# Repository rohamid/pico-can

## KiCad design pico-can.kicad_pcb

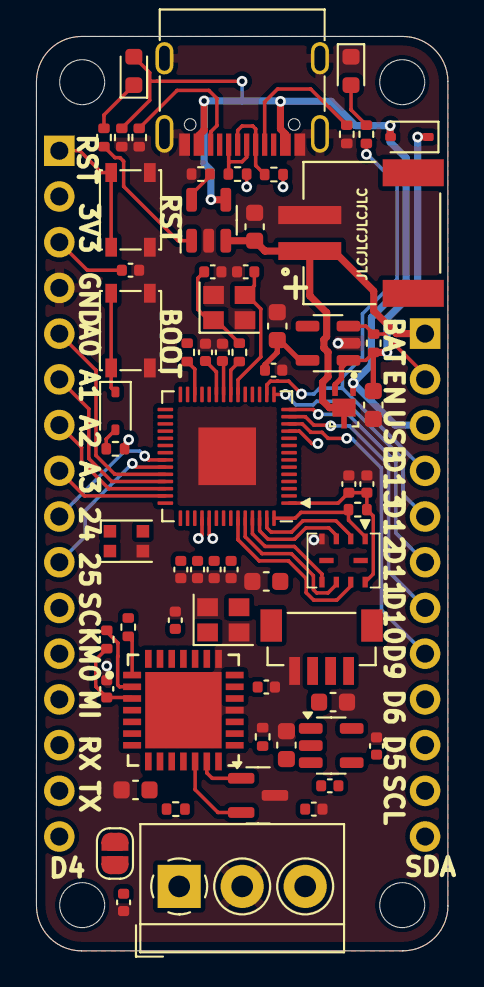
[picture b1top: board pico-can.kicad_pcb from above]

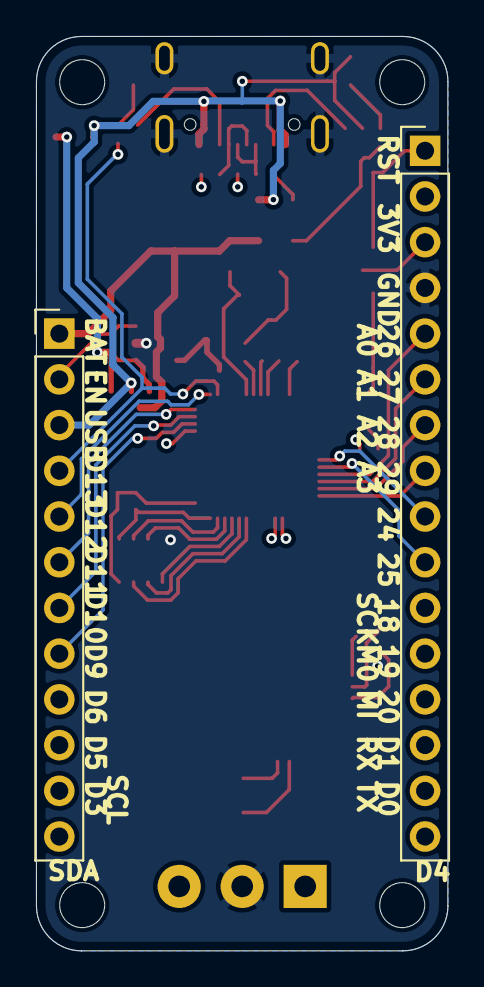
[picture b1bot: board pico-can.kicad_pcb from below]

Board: 2 copper layers, 22.9 x 50.8 mm, 71 parts (2 on the bottom side), 62 nets.

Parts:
C1, C2, C6, C18: 22p; C_0402_1005Metric
C3, C4, C5: 10u; C_0603_1608Metric
C7, C8, C10, C11, C12, C13, C14, C15, C16, C22, C23, C24: 100nF; C_0402_1005Metric
C9: 1uF; C_0402_1005Metric
C17, C21, C25, C26: 1uF; C_0603_1608Metric
C19, C20: 47pF; C_0402_1005Metric
D1: MBR0540; D_SOD-323
D2, D4: LED; LED_0603_1608Metric
D3: NSR0320; D_SOD-323
D5: WS2812B; LED_WS2812B-2020_PLCC4_2.0x2.0mm
D6: PESD1CAN; SOT-23
H1, H2, H3, H4: MountingHole; MountingHole_2.5mm
J1: USB_C_Receptacle_USB2.0; USB_C_Receptacle_G-Switch_GT-USB-7010ASV
J2: I2C; JST_BM04B-SRSS-TB_LF__SN_
J3: Screw_Terminal_01x03; TerminalBlock_4Ucon_1x03_P3.50mm_Horizontal
J4: Conn; PinHeader_1x16_P2.54mm_Vertical
J5: Conn; PinHeader_1x12_P2.54mm_Vertical
J6: BAT; JST_S2B-PH-SM4-TB_LF__SN_
JP1: JMP; SolderJumper-2_P1.3mm_Open_RoundedPad1.0x1.5mm
Q1: BSS83P; TRANS_DMG3415UFY4Q-7
R1, R3, R8, R9, R11, R12, R13, R14, R15, R16: 10K; R_0402_1005Metric
R2: 1K; R_0402_1005Metric
R4, R5, R10: 5K1; R_0402_1005Metric
R6, R7: 220; R_0402_1005Metric
R17: 120; R_0402_1005Metric
SW1, SW2: SW_Push; SW_SPST_PTS810
U1: RP2040; QFN-56-1EP_7x7mm_P0.4mm_EP3.2x3.2mm
U2: W25Q128JVS; USON-8-3x4
U3: AP2112K-3.3; SOT-23-5
U4: MCP73831; SOT-23-5
U5: AP3012; SOT-23-5
U7: MCP25625T-E_ML; Microchip-ML-28-0-0-0
Y1: 24MHz; Crystal_SMD_2520-4Pin_2.5x2.0mm
Y2: 16MHz; Crystal_SMD_2520-4Pin_2.5x2.0mm

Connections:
+1V2: C7.1, C8.1, C9.1, U1.23 (DVDD), U1.45 (VREG_VOUT), U1.50 (DVDD)
+3V3: C4.1, C10.1, C11.1, C12.1, C13.1, C14.1, C15.1, C16.1, C17.1, C21.1, C22.1, C23.1, C25.1, C26.1, J2.2, J4.2, J4.3, R1.1, R3.1, R14.1, R15.1, U1.1 (IOVDD), U1.10 (IOVDD), U1.22 (IOVDD), U1.33 (IOVDD), U1.42 (IOVDD), U1.43 (ADC_AVDD), U1.44 (VREG_IN), U1.48 (USB_VDD), U1.49 (IOVDD), U2.8 (VCC), U3.5 (VOUT), U7.3 (VDD), U7.11 (VIO)
/CAN-Bus/CANH: C19.1, D6.1 (K), J3.3, JP1.2 (B), U7.13 (CANH)
/CAN-Bus/CANL: C20.1, D6.2 (K), J3.1, R17.2, U7.12 (CANL)
/CAN-Bus/CAN_STBY: R16.2, U7.15 (STBY)
/CAN-Bus/RxCAN: U7.5 (RxCAN), U7.10 (RXD)
/CAN-Bus/TxCAN: U7.4 (TxCAN), U7.16 (TXD)
/CAN-Bus/~CAN_CS: R14.2, U7.1 (~CS)
/CAN-Bus/~CAN_RESET: R15.2, U7.2 (~RESET)
/EN: J5.2, R9.2, U3.3 (EN)
/GPIO0: J4.15, U1.2 (GPIO0)
/GPIO1: J4.14, U1.3 (GPIO1)
/GPIO2: J2.3, J5.12, U1.4 (GPIO2)
/GPIO3: J2.4, J5.11, U1.5 (GPIO3)
/GPIO4: J4.16, U1.6 (GPIO4)
/GPIO5: J5.10, U1.7 (GPIO5)
/GPIO6: J5.9, U1.8 (GPIO6)
/GPIO8: J4.13, U1.11 (GPIO8)
/GPIO9: J5.8, U1.12 (GPIO9)
/GPIO10: J5.7, U1.13 (GPIO10)
/GPIO11: J5.6, U1.14 (GPIO11)
/GPIO12: J5.5, U1.15 (GPIO12)
/GPIO13: J5.4, R13.1, U1.16 (GPIO13)
/GPIO14: J4.11, U1.17 (GPIO14)
/GPIO15: J4.12, U1.18 (GPIO15)
/GPIO20: D5.1 (VDD), U1.31 (GPIO20)
/GPIO21: D5.4 (DIN), U1.32 (GPIO21)
/GPIO24: J4.9, U1.36 (GPIO24)
/GPIO25: J4.10, U1.37 (GPIO25)
/GPIO26_ADC0: J4.5, U1.38 (GPIO26_ADC0)
/GPIO27_ADC1: J4.6, U1.39 (GPIO27_ADC1)
/GPIO28_ADC2: J4.7, U1.40 (GPIO28_ADC2)
/GPIO29_ADC3: J4.8, U1.41 (GPIO29_ADC3)
/QSPI_SCLK: U1.52 (QSPI_SCLK), U2.6 (CLK)
/QSPI_SD0: U1.53 (QSPI_SD0), U2.5 (DI(IO0))
/QSPI_SD1: U1.55 (QSPI_SD1), U2.2 (DO(IO1))
/QSPI_SD2: U1.54 (QSPI_SD2), U2.3 (IO2)
/QSPI_SD3: U1.51 (QSPI_SD3), U2.7 (IO3)
/QSPI_SS: R3.2, R12.1, U1.56 (QSPI_SS), U2.1 (~CS)
/USB_DN: R6.2, U1.46 (USB_DM)
/USB_DP: R7.2, U1.47 (USB_DP)
/~RST: J4.1, R1.2, SW2.2, U1.26 (RUN)
GND: C1.1, C2.1, C3.2, C4.2, C5.2, C6.2, C7.2, C8.2, C9.2, C10.2, C11.2, C12.2, C13.2, C14.2, C15.2, C16.2, C17.2, C18.2, C19.2, C20.2, C21.2, C22.2, C23.2, C25.2, C26.2, D4.1 (K), D5.3 (VSS), D6.3 (A), J1.A1 (GND), J1.A12 (GND), J1.B1 (GND), J1.B12 (GND), J1.S1 (SHIELD), J2.1, J3.2, J4.4, J6.2, R4.2, R5.2, R8.2, R10.2, R16.1, SW1.1, SW2.1, U1.19 (TESTEN), U1.57 (GND), U2.4 (GND), U3.2 (GND), U4.2 (V_{SS}), U7.18 (VSS), U7.22 (GND), U7.29 (EP), Y1.2, Y1.4, Y2.2, Y2.4
unnamed: C2.2, R2.1, Y1.1
unnamed: D2.1 (K), R11.2
unnamed: D3.2 (A), R12.2
unnamed: D3.1 (K), SW1.2
unnamed: D4.2 (A), R13.2
unnamed: J1.A5 (CC1), R4.1
unnamed: J1.B5 (CC2), R5.1
unnamed: J1.A6 (D+), J1.B6 (D+), R7.1
unnamed: J1.A7 (D-), J1.B7 (D-), R6.1
unnamed: JP1.1 (A), R17.1
unnamed: C1.2, U1.20 (XIN), Y1.3
unnamed: R2.2, U1.21 (XOUT)
unnamed: R10.1, U4.5 (PROG)
unnamed: R11.1, U4.1 (STAT)
unnamed: C18.1, U7.21 (OSC1), Y2.1
unnamed: C6.1, U7.20 (OSC2), Y2.3
VBAT: C5.1, J5.1, J6.1, Q1.3 (D), U4.3 (V_{BAT})
VBUS: D1.2 (A), D2.2 (A), J1.A4 (VBUS), J1.A9 (VBUS), J1.B4 (VBUS), J1.B9 (VBUS), J5.3, Q1.1 (G), R8.1, U4.4 (V_{DD})
VHI: C3.1, D1.1 (K), Q1.2 (S), R9.1, U3.1 (VIN)

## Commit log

2024-03-19 Updated .gitignore
2024-03-25 add screen shoot image
